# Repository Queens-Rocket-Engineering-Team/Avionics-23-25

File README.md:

# Legacy Repo!!
All QRET avionics hardware and firmware has migrated to:
- https://github.com/Queens-Rocket-Engineering-Team/av-recovery
- https://github.com/Queens-Rocket-Engineering-Team/av-instrumentation
- https://github.com/Queens-Rocket-Engineering-Team/av-telemetry
- http://github.com/Queens-Rocket-Engineering-Team/av-prop
- https://github.com/Queens-Rocket-Engineering-Team/av-power
- https://github.com/Queens-Rocket-Engineering-Team/av-libraries

# QRET Avionics (2023-2026)

This repository is the working space for QRET's 2023-2026 Avionics systems. This includes both hardware design and firmware projects.

If you're contributing, **make sure you're working in a branch other than Main.**

## Branch Naming Conventions
If you create a new branch, make sure its name includes:
- The subject you're working on
- Hardware (HW) or Firmware (FW)

Examples: `Altimeter_HW`, `Sensors_FW`

Currently we're using KiCAD 8.0.6.

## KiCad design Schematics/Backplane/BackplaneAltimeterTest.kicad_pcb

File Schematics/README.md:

# Schematics

This directory contains all schematics involved in this iteration of the Avionics system.

Schematics are made using KiCAD 7.

The `Templates` directory contains a KiCAD project with miscellaneous templates, such as the stack edge connector and template module PCB layout.

## Backplane
- Single large PCB
- Connects all stack "modules" (PCBs)
- Allows communication between modules (CANBUS)
- Cleaner routing for power

## GPS Module
- Acquires GPS signal
- Logs GPS data locally
- Has a daughter-board for the GPS receiver

## Communications Module
- Tracks data from other modules using CANBUS
- Remotely transmits data to ground station

## Altimter Module
- Tracks altitude using pressure and acceleration
- Deploys parachute charges
- Runs on secondary power supply rail
- Logs altitude, pressure, events, etc. locally

## Sensors Module
- Has various on-board and external sensors
- Logs data from above sensors locally

## Power Module
- Provides power to all other modules
	- Primary and Secondary 3.3V rails
	- Primary 5.0V rail
- Facilitates connections between backplane and external devices
	- Batteries
	- Screw switches

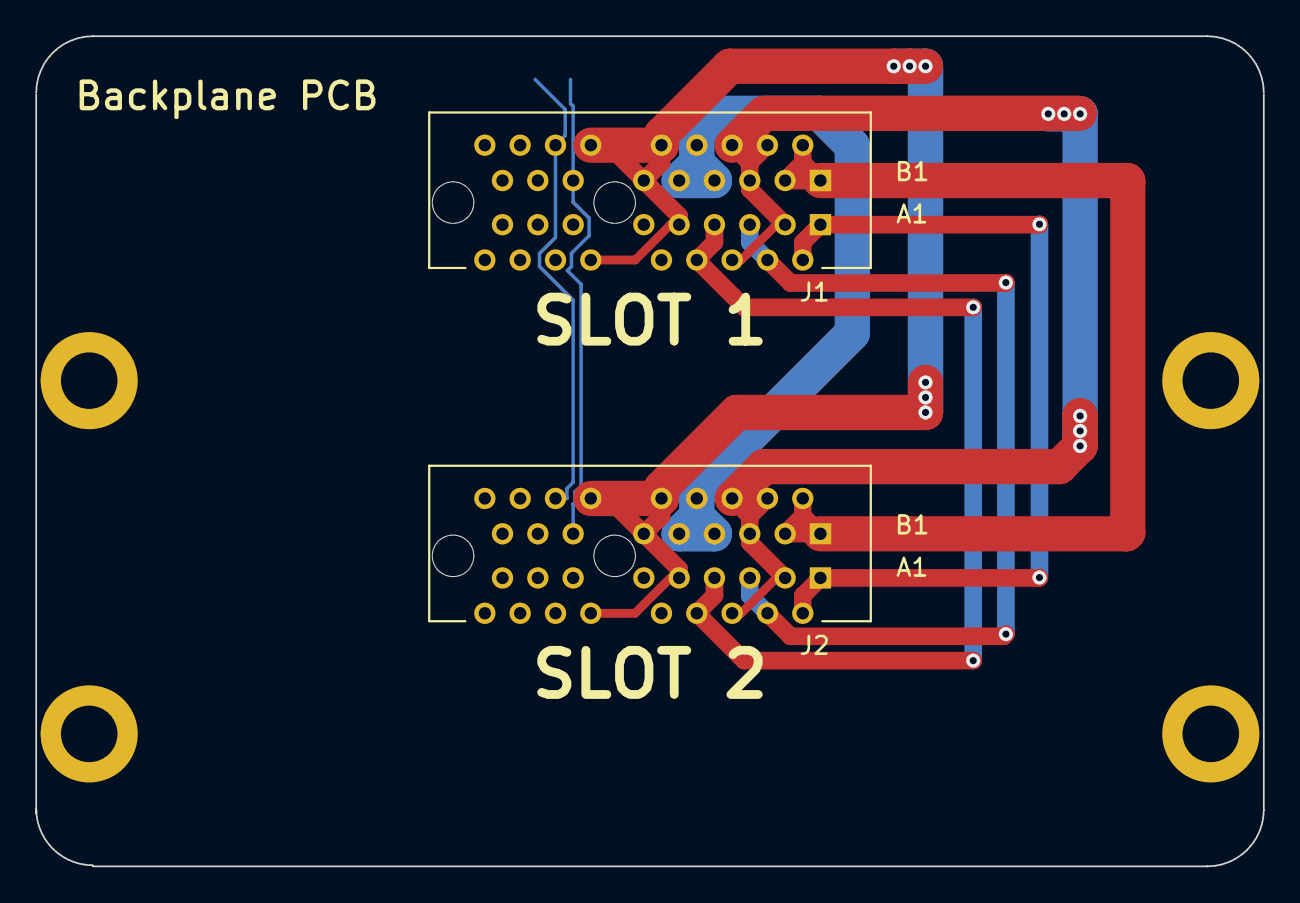
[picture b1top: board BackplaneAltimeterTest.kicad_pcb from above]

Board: 2 copper layers, 69.5 x 47.0 mm, 7 parts (1 on the bottom side), 9 nets.

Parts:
H1, H2, H5, H6: MountingHole; MountingHole_3.2mm_M3_ISO14580_Pad
J1: Edge Connector (SLOT 1); AMPHENOL_10018784-10210TLF
J2: Edge Connector (SLOT 2); AMPHENOL_10018784-10210TLF
R1: 120R; R_0805_2012Metric_Pad1.20x1.40mm_HandSolder

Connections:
3.3V_A: J1.A1 (3.3V_A), J1.A2 (3.3V_A), J2.A1 (3.3V_A), J2.A2 (3.3V_A)
3.3V_B: J1.A7 (3.3V_B), J1.A8 (3.3V_B), J2.A7 (3.3V_B), J2.A8 (3.3V_B)
5.0V_A: J1.A4 (5.0V_A), J1.A5 (5.0V_A), J2.A4 (5.0V_A), J2.A5 (5.0V_A)
BATT_A: J1.B1 (BATT_A), J1.B2 (BATT_A), J1.B3 (BATT_A), J2.B1 (BATT_A), J2.B2 (BATT_A), J2.B3 (BATT_A)
BATT_B: J1.B7 (BATT_B), J1.B8 (BATT_B), J1.B9 (BATT_B), J2.B7 (BATT_B), J2.B8 (BATT_B), J2.B9 (BATT_B)
CAN_H: J1.B14 (CAN_H), J2.B14 (CAN_H), R1.1
CAN_L: J1.B13 (CAN_L), J2.B13 (CAN_L), R1.2
GND1: J1.A3 (GND_A), J1.A6 (GND_A), J1.B4 (GND_A), J1.B5 (GND_A), J1.B6 (GND_A), J2.A3 (GND_A), J2.A6 (GND_A), J2.B4 (GND_A), J2.B5 (GND_A), J2.B6 (GND_A)
GND2: J1.A9 (GND_B), J1.A12 (GND_B), J1.B10 (GND_B), J1.B11 (GND_B), J1.B12 (GND_B), J2.A9 (GND_B), J2.A12 (GND_B), J2.B10 (GND_B), J2.B11 (GND_B), J2.B12 (GND_B)

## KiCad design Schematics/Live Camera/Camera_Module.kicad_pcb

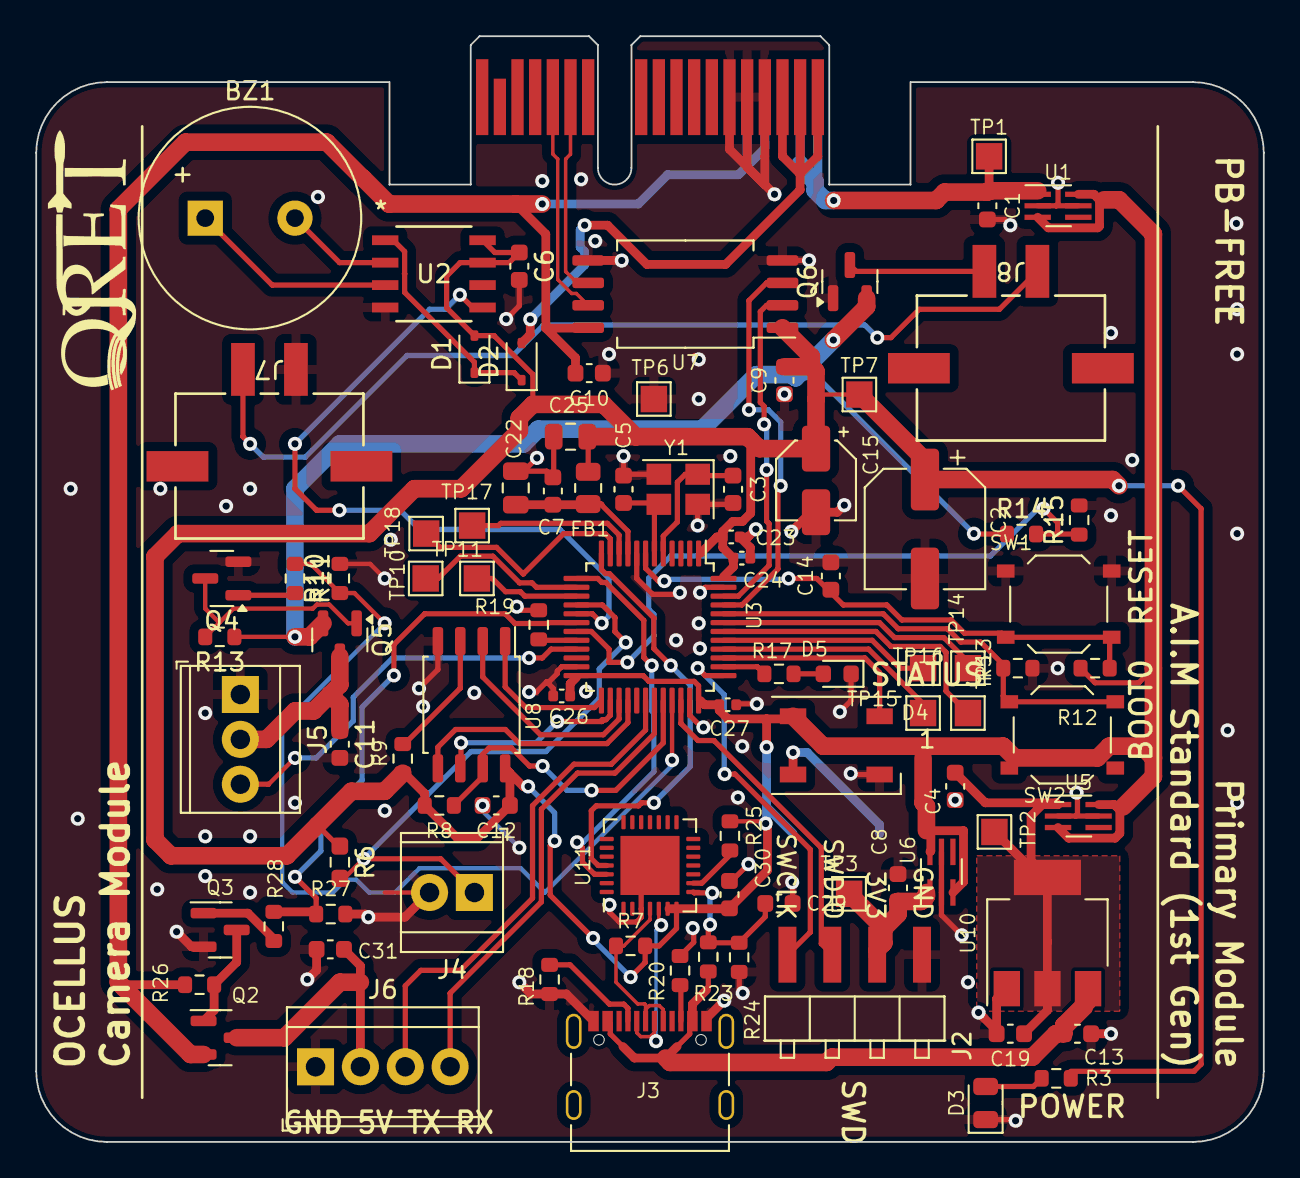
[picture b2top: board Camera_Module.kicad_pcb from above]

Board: 2 copper layers, 69.5 x 62.6 mm, 93 parts (1 on the bottom side), 68 nets.

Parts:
BZ1: PS1240P02BT; Buzzer_12.6x9.5RM5.0
C1, C4, C8, C29: 1uF; C_0603_1608Metric
C2: 100uF; CP_Elec_6.3x5.9
C3, C5: 10p; C_0603_1608Metric
C6, C12, C14: 100nF; C_0603_1608Metric
C7: 10n; C_0603_1608Metric
C9, C10: 0.1u; C_0603_1608Metric
C11, C13, C19, C30, C31: 10uF; C_0603_1608Metric
C15: 10uF; CP_Elec_4x5.4
C22, C25: 1uF; C_0805_2012Metric
C23, C24, C26, C27: 100n; C_0402_1005Metric
D1, D2: 1N5819WS; D_SOD-323
D3: PWR_LED (GRN); LED_0805_2012Metric
D4, D6: WS2812B; LED_WS2812B_PLCC4_5.0x5.0mm_P3.2mm
D5: DB_LED (YLW); LED_0603_1608Metric
FB1: 100R; R_0805_2012Metric
J1: Stack Male Edge Connector; BUS_PCIexpress_x1
J2: SWD_01x04_Pin; SWD_PinHeader_1x04_P2.54mm_Horizontal_SMD
J3: USB_C_Female_USB2_Small; USB_C_DB-108PWB
J4: Therm_In; TerminalBlock_TE_282834-2_1x02_P2.54mm_Horizontal
J5: VTX; TerminalBlock_TE_282834-3_1x03_P2.54mm_Horizontal
J6: RunCam6; TerminalBlock_TE_282834-4_1x04_P2.54mm_Horizontal
J7: VTX_BATT_IN; CONN_2-1445057-2_TYCO
J8: VTX_BATT_SWITCH; CONN_2-1445057-2_TYCO
Q2, Q5, Q6: AO3401A; SOT-23
Q3, Q4: AO3400A; SOT-23
R3: 3.3k; R_0603_1608Metric
R5, R10, R13, R14, R19, R26, R27: 100k; R_0603_1608Metric
R6: 10k; R_0603_1608Metric_Pad0.98x0.95mm_HandSolder
R7: 1.5k; R_0603_1608Metric
R8, R9, R12: 10k; R_0603_1608Metric
R11, R28: 510; R_0603_1608Metric
R15: 20k; R_0603_1608Metric
R17: 680R; R_0603_1608Metric
R18, R20: 5.1k; R_0603_1608Metric
R23: 22k; R_0603_1608Metric
R24: 47k; R_0603_1608Metric
R25: 1k; R_0603_1608Metric
SW1: SW_STM_RESET; SW_Push_1P1T_XKB_TS-1187A
SW2: SW_STM_BOOT_MODE; SW_Push_1P1T_XKB_TS-1187A
TP1: TP_VSTACK; TestPoint_Pad_1.5x1.5mm
TP2: TP_VUSB; TestPoint_Pad_1.5x1.5mm
TP3: TP_VSWD; TestPoint_Pad_1.5x1.5mm
TP6: TP_GND; TestPoint_Pad_1.5x1.5mm
TP7: TP_3V3; TestPoint_Pad_1.5x1.5mm
TP10: PA4; TestPoint_Pad_1.5x1.5mm
TP11: PA5; TestPoint_Pad_1.5x1.5mm
TP13: PB6; TestPoint_Pad_1.5x1.5mm
TP14: PB5; TestPoint_Pad_1.5x1.5mm
TP15: PB4; TestPoint_Pad_1.5x1.5mm
TP16: PB7; TestPoint_Pad_1.5x1.5mm
TP17: PA0; TestPoint_Pad_1.5x1.5mm
TP18: PA1; TestPoint_Pad_1.5x1.5mm
U1, U5, U6: LM66100DCKR; SC-70-6_Handsoldering
U2: TPM8837C-SO1R; SOP-8_TPK
U3: STM32F103CBT6; LQFP-48_7x7mm_P0.5mm
U7: ISO1042BDWVR; SOIC-8 ISO1042BDWV
U8: W25Q128JVS; SOIC-8_5.23x5.23mm_P1.27mm
U10: AMS1117-3.3; SOT-223-3_TabPin2
U11: CP2102N-Axx-xQFN28; QFN-28-1EP_5x5mm_P0.5mm_EP3.35x3.35mm
Y1: X322516MMB4SI; Crystal_SMD_3225-4Pin_3.2x2.5mm

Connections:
5V_USB: C13.1, J3.A4 (VBUS), J3.A9 (VBUS), J3.B4 (VBUS), J3.B9 (VBUS), R23.2, U10.3 (VI)
+3.3V: C2.1, C6.1, C9.2, C12.1, C15.1, C23.1, C24.1, C25.1, C26.1, C27.1, C30.2, D1.2 (A), D4.1 (VDD), D6.1 (VDD), FB1.2, R3.2, R6.1, R7.1, R8.2, R9.2, R12.2, R25.2, SW2.2, TP7.1, U1.3 (*CE), U1.6 (VOUT), U2.7 (NSLEEP), U2.8 (VCC), U3.1 (VBAT), U3.24 (VDD), U3.36 (VDD), U3.48 (VDD), U5.3 (*CE), U5.6 (VOUT), U6.3 (*CE), U6.6 (VOUT), U7.1 (VCC1), U8.8 (VCC), U11.6 (VDD), U11.7 (VREGIN)
+3.3VA: C7.1, C22.1, FB1.1, U3.9 (VDDA)
+5V: C10.2, J1.A4 (5.0V_A), J1.A5 (5.0V_A), Q2.2 (S), R26.1, U7.8 (VCC2)
+BATT: D2.2 (A), J1.B1 (BATT_A), J1.B2 (BATT_A), J1.B3 (BATT_A)
BOOT0: R5.2, SW2.1, U3.44 (BOOT0)
BOOT1: R19.2, U3.20 (PB2)
BUZZER_A: U2.6 (IN1), U3.29 (PA8)
BUZZER_B: U2.5 (IN2), U3.17 (PA7)
CAM_5V: C31.1, J6.2, Q2.3 (D)
CAM_PWR: R27.1, R28.1, U3.18 (PB0)
CAM_RX: J6.4, U3.31 (PA10)
CAM_TX: J6.3, U3.30 (PA9)
CAN_H: J1.B14 (CAN_H), U7.7 (CANH)
CAN_L: J1.B13 (CAN_L), U7.6 (CANL)
CAN_RX: U3.45 (PB8), U7.3 (RXD)
CAN_TX: U3.46 (PB9), U7.2 (TXD)
CS_FL: U3.25 (PB12), U8.1 (~CS)
DB_LED: R17.2, U3.38 (PA15)
GND: C1.2, C2.2, C3.2, C4.2, C5.2, C6.2, C7.2, C8.2, C9.1, C10.1, C11.2, C12.2, C13.2, C14.2, C15.2, C19.2, C22.2, C23.2, C24.2, C25.2, C26.2, C27.2, C29.1, C30.1, C31.2, D3.1 (K), D4.3 (VSS), D5.1 (K), D6.3 (VSS), J1.A3 (GND_A), J1.A6 (GND_A), J1.B4 (GND_A), J1.B5 (GND_A), J1.B6 (GND_A), J2.1 (GND), J3.A1 (GND), J3.A12 (GND), J3.B1 (GND), J3.B12 (GND), J4.2, J5.1, J6.1, J7.1, Q3.2 (S), Q4.2 (S), Q6.1 (G), R5.1, R10.2, R15.2, R18.2, R19.1, R20.2, R24.1, R27.2, SW1.1, TP6.1, U1.2 (GND), U1.5 (ST), U2.4 (GND), U3.8 (VSSA), U3.23 (VSS), U3.35 (VSS), U3.47 (VSS), U5.2 (GND), U5.5 (ST), U6.2 (GND), U6.5 (ST), U7.4 (GND1), U7.5 (GND2), U8.4 (GND), U10.1 (GND), U11.3 (GND), U11.29 (GND), Y1.2, Y1.4
MISO_FL: U3.27 (PB14), U8.2 (DO(IO1))
MOSI_FL: U3.28 (PB15), U8.5 (DI(IO0))
unnamed: BZ1.2 (+), U2.2 (OUT1)
unnamed: BZ1.1 (-), U2.3 (OUT2)
unnamed: D1.1 (K), D2.1 (K), U2.1 (VM)
unnamed: D3.2 (A), R3.1
unnamed: D4.2 (DOUT), D6.4 (DIN)
unnamed: D5.2 (A), R17.1
unnamed: J3.A5 (CC1), R18.1
unnamed: J3.B5 (CC2), R20.1
unnamed: J7.2, J8.1
unnamed: Q2.1 (G), Q3.3 (D), R26.2
unnamed: Q3.1 (G), R28.2
unnamed: Q4.3 (D), Q5.1 (G), R13.2
unnamed: Q4.1 (G), R11.2
unnamed: J8.2, Q6.3 (D)
unnamed: TP17.1, U3.10 (PA0)
unnamed: TP18.1, U3.11 (PA1)
unnamed: TP10.1, U3.14 (PA4)
unnamed: TP11.1, U3.15 (PA5)
unnamed: TP15.1, U3.40 (PB4)
unnamed: TP14.1, U3.41 (PB5)
unnamed: TP13.1, U3.42 (PB6)
unnamed: TP16.1, U3.43 (PB7)
unnamed: R9.1, U8.3 (IO2)
unnamed: C29.2, R23.1, R24.2, U11.8 (VBUS)
unnamed: R25.1, U11.9 (~RST)
OSC_IN: C3.1, U3.5 (PD0), Y1.1
OSC_OUT: C5.1, U3.6 (PD1), Y1.3
RESET_FL: R8.1, U3.32 (PA11), U8.7 (IO3)
RGB_DATA: D4.4 (DIN), U3.39 (PB3)
SCK_FL: U3.26 (PB13), U8.6 (CLK)
STM_RESET: C14.1, R12.1, SW1.2, U3.7 (NRST)
SWCLK: J2.4 (SWCLK), U3.37 (PA14)
SWDIO: J2.3 (SWDIO), U3.34 (PA13)
USB_D+: J3.A6 (D+), J3.B6 (D+), R7.2, U11.4 (D+)
USB_D-: J3.A7 (D-), J3.B7 (D-), U11.5 (D-)
USB_RX: U3.13 (PA3), U11.26 (TXD)
USB_TX: U3.12 (PA2), U11.25 (RXD)
VTX_BATT: Q5.2 (S), Q6.2 (S), R13.1, R14.1
VTX_BATT_SENSE: R14.2, R15.1, U3.19 (PB1)
VTX_DATA: J5.3, U3.21 (PB10)
VTX_PWR: R10.1, R11.1, U3.33 (PA12)
VTX_V+: C11.1, J5.2, Q5.3 (D)
V_PSU: C1.1, J1.A1 (3.3V_A), J1.A2 (3.3V_A), TP1.1, U1.1 (VIN)
V_REGUSB: C4.1, C19.1, TP2.1, U5.1 (VIN), U10.2 (VO)
V_SWD: C8.1, J2.2 (3V3), TP3.1, U6.1 (VIN)
V_THERM: J4.1, R6.2, U3.16 (PA6)

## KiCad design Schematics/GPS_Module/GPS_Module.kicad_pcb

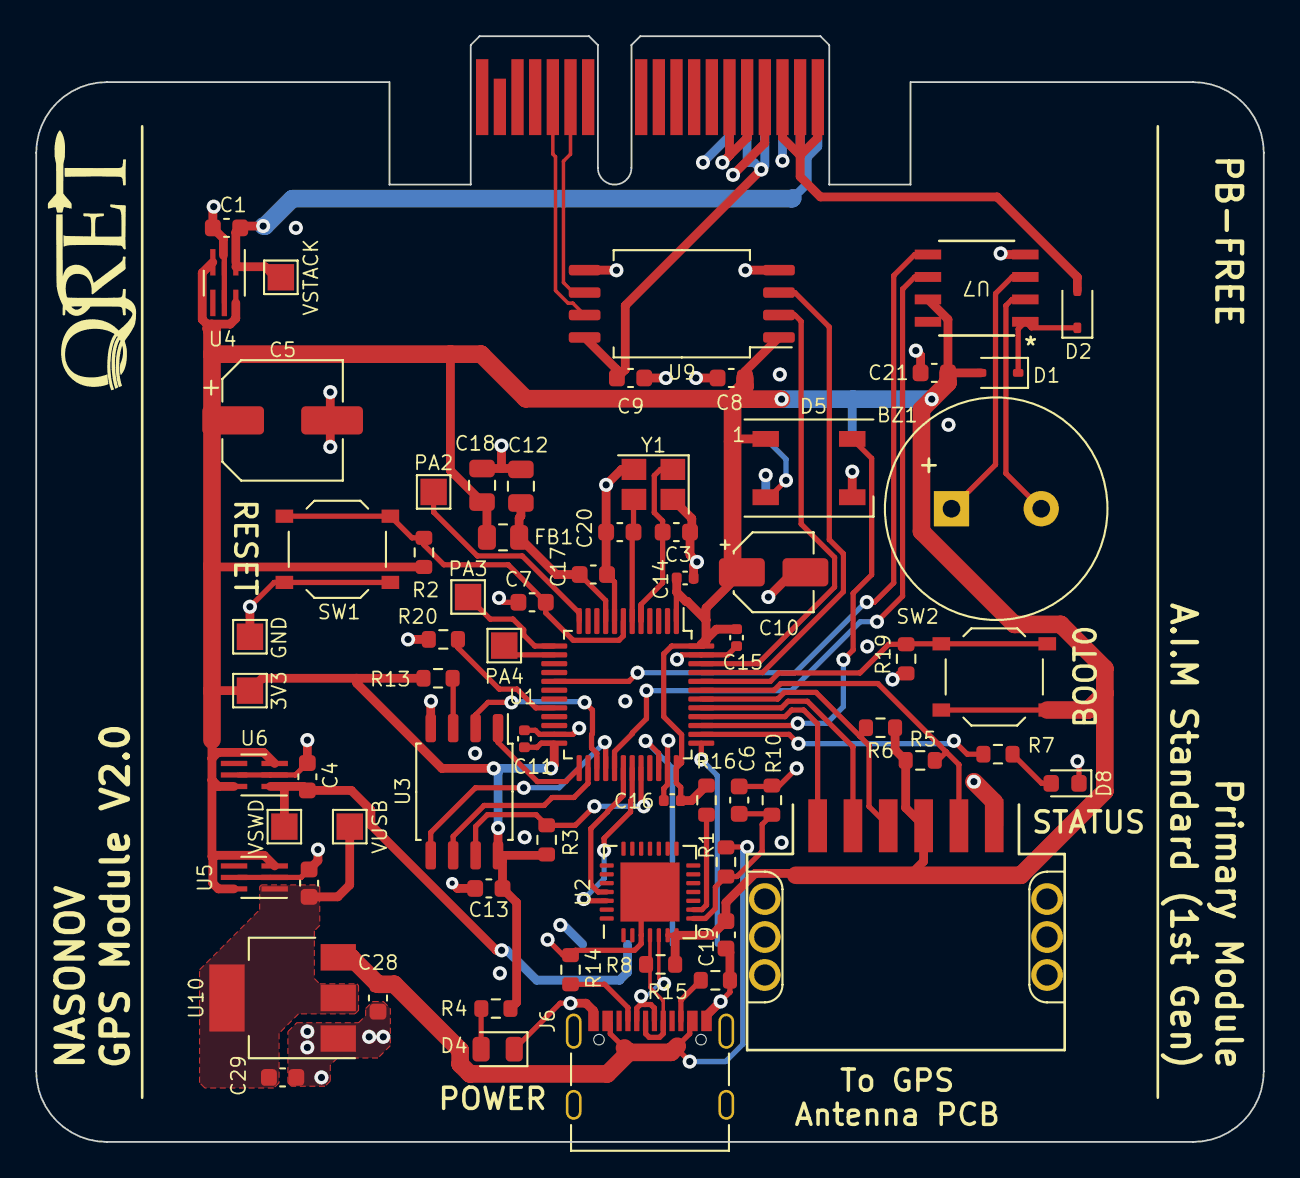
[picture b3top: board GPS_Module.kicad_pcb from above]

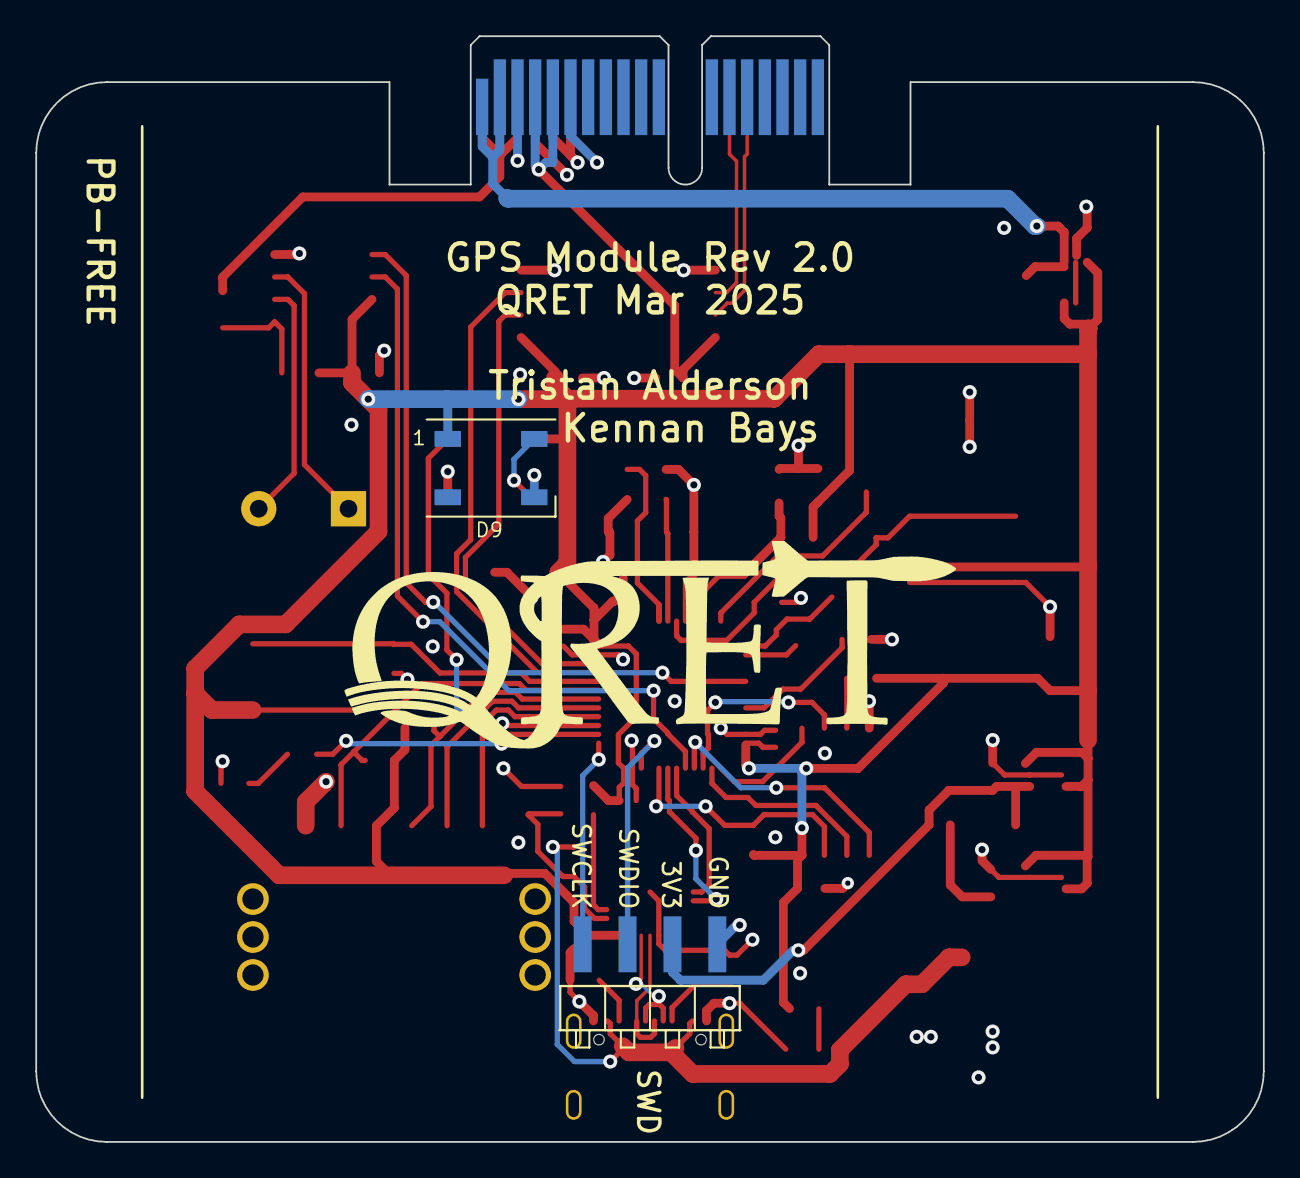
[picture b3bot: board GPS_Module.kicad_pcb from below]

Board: 4 copper layers, 69.5 x 62.6 mm, 70 parts (2 on the bottom side), 51 nets.

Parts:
BZ1: PS1240P02BT; Buzzer_12.6x9.5RM5.0
C1, C2, C4, C6: 1uF; C_0603_1608Metric
C3, C20: 10p; C_0603_1608Metric
C5: 100uF; CP_Elec_6.3x5.9
C7, C13, C21: 100nF; C_0603_1608Metric
C8, C9: 0.1u; C_0603_1608Metric
C10: 10uF; CP_Elec_4x5.4
C11, C14, C15, C16: 100n; C_0402_1005Metric
C12, C18: 1uF; C_0805_2012Metric
C17: 10n; C_0603_1608Metric
C19, C28, C29: 10uF; C_0603_1608Metric
D1, D2: 1N5819WS; D_SOD-323
D4: PWR_LED (GRN); LED_0805_2012Metric
D5, D9: WS2812B; LED_WS2812B_PLCC4_5.0x5.0mm_P3.2mm
D8: DB_LED (YLW); LED_0603_1608Metric
FB1: 100R; R_0805_2012Metric
J1: GT8E-6P-2H(55); CONN_GT8E-6P-2H(55)
J2: SWD_01x04_Pin; SWD_PinHeader_1x04_P2.54mm_Horizontal_SMD
J4: Stack Male Edge Connector; BUS_PCIexpress_x1
J6: USB_C_Female_USB2_Small; USB_C_DB-108PWB
R1: 22k; R_0603_1608Metric
R2, R3, R13: 10k; R_0603_1608Metric
R4: 3.3k; R_0603_1608Metric
R5, R6: 2.2k; R_0603_1608Metric
R7: 680R; R_0603_1608Metric
R8: 1.5k; R_0603_1608Metric
R10: 47k; R_0603_1608Metric
R14, R15: 5.1k; R_0603_1608Metric
R16: 1k; R_0603_1608Metric
R19, R20: 100k; R_0603_1608Metric
SW1: SW_STM_RESET; SW_Push_1P1T_XKB_TS-1187A
SW2: SW_STM_BOOT_MODE; SW_Push_1P1T_XKB_TS-1187A
TP1: VSTACK; TestPoint_Pad_1.5x1.5mm
TP2: VUSB; TestPoint_Pad_1.5x1.5mm
TP3: VSWD; TestPoint_Pad_1.5x1.5mm
TP4: PA4; TestPoint_Pad_1.5x1.5mm
TP6: GND; TestPoint_Pad_1.5x1.5mm
TP7: 3V3; TestPoint_Pad_1.5x1.5mm
TP10: PA2; TestPoint_Pad_1.5x1.5mm
TP11: PA3; TestPoint_Pad_1.5x1.5mm
U1: STM32F103CBT6; LQFP-48_7x7mm_P0.5mm
U2: CP2102N-Axx-xQFN28; QFN-28-1EP_5x5mm_P0.5mm_EP3.35x3.35mm
U3: W25Q128JVS; SOIC-8_5.23x5.23mm_P1.27mm
U4, U5, U6: LM66100DCKR; SC-70-6_Handsoldering
U7: TPM8837C-SO1R; SOP-8_TPK
U9: ISO1042BQDWVR; SOIC-8 ISO1042BDWV
U10: AMS1117-3.3; SOT-223-3_TabPin2
Y1: X322516MMB4SI; Crystal_SMD_3225-4Pin_3.2x2.5mm

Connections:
5V_RAW: C28.1, J6.A4 (VBUS), J6.A9 (VBUS), J6.B4 (VBUS), J6.B9 (VBUS), R1.2, U10.3 (VI)
+3.3V: C5.1, C8.2, C10.1, C11.1, C13.1, C14.1, C15.1, C16.1, C18.1, C19.2, C21.1, D1.2 (A), D5.1 (VDD), D9.1 (VDD), FB1.2, J1.3, R2.2, R3.2, R4.2, R5.2, R6.1, R8.1, R13.2, R16.2, SW2.2, TP7.1, U1.1 (VBAT), U1.24 (VDD), U1.36 (VDD), U1.48 (VDD), U2.6 (VDD), U2.7 (VREGIN), U3.8 (VCC), U4.3 (*CE), U4.6 (VOUT), U5.3 (*CE), U5.6 (VOUT), U6.3 (*CE), U6.6 (VOUT), U7.7 (NSLEEP), U7.8 (VCC), U9.1 (VCC1)
+3.3VA: C12.1, C17.1, FB1.1, U1.9 (VDDA)
+5V: C9.2, J4.A4 (5.0V_A), J4.A5 (5.0V_A), U9.8 (VCC2)
+BATT: D2.2 (A), J4.B1 (BATT_A), J4.B2 (BATT_A), J4.B3 (BATT_A)
BOOT0: R19.2, SW2.1, U1.44 (BOOT0)
BOOT1: R20.2, U1.20 (PB2)
BUZZER_A: U1.29 (PA8), U7.6 (IN1)
BUZZER_B: U1.17 (PA7), U7.5 (IN2)
CAN_H: J4.B14 (CAN_H), U9.7 (CANH)
CAN_L: J4.B13 (CAN_L), U9.6 (CANL)
CAN_RX: U1.45 (PB8), U9.3 (RXD)
CAN_TX: U1.46 (PB9), U9.2 (TXD)
CS_FL: U1.25 (PB12), U3.1 (~CS)
DB_LED: R7.2, U1.38 (PA15)
EXTINT_GPS: J1.5, U1.41 (PB5)
GND: C1.2, C2.2, C3.2, C4.2, C5.2, C6.1, C7.2, C8.1, C9.1, C10.2, C11.2, C12.2, C13.2, C14.2, C15.2, C16.2, C17.2, C18.2, C19.1, C20.2, C21.2, C28.2, C29.2, D4.1 (K), D5.3 (VSS), D8.1 (K), D9.3 (VSS), J1.1, J2.1 (GND), J4.A3 (GND_A), J4.A6 (GND_A), J4.B4 (GND_A), J4.B5 (GND_A), J4.B6 (GND_A), J6.A1 (GND), J6.A12 (GND), J6.B1 (GND), J6.B12 (GND), R10.1, R14.2, R15.2, R19.1, R20.1, SW1.1, TP6.1, U1.8 (VSSA), U1.23 (VSS), U1.35 (VSS), U1.47 (VSS), U2.3 (GND), U2.29 (GND), U3.4 (GND), U4.2 (GND), U4.5 (ST), U5.2 (GND), U5.5 (ST), U6.2 (GND), U6.5 (ST), U7.4 (GND), U9.4 (GND1), U9.5 (GND2), U10.1 (GND), Y1.2, Y1.4
MISO_FL: U1.27 (PB14), U3.2 (DO(IO1))
MOSI_FL: U1.28 (PB15), U3.5 (DI(IO0))
unnamed: BZ1.2 (+), U7.2 (OUT1)
unnamed: BZ1.1 (-), U7.3 (OUT2)
unnamed: D1.1 (K), D2.1 (K), U7.1 (VM)
unnamed: D4.2 (A), R4.1
unnamed: D5.2 (DOUT), D9.4 (DIN)
unnamed: D8.2 (A), R7.1
unnamed: J6.A5 (CC1), R14.1
unnamed: J6.B5 (CC2), R15.1
unnamed: TP10.1, U1.12 (PA2)
unnamed: TP11.1, U1.13 (PA3)
unnamed: TP4.1, U1.14 (PA4)
unnamed: C6.2, R1.1, R10.2, U2.8 (VBUS)
unnamed: R16.1, U2.9 (~RST)
unnamed: R13.1, U3.3 (IO2)
OSC_IN: C3.1, U1.5 (PD0), Y1.1
OSC_OUT: C20.1, U1.6 (PD1), Y1.3
RESET_FL: R3.1, U1.32 (PA11), U3.7 (IO3)
RGB_DATA: D5.4 (DIN), U1.39 (PB3)
RST_GPS: J1.6, U1.40 (PB4)
SCK_FL: U1.26 (PB13), U3.6 (CLK)
SCL_GPS: J1.4, R6.2, U1.42 (PB6)
SDA_GPS: J1.2, R5.1, U1.43 (PB7)
STM_RESET: C7.1, R2.1, SW1.2, U1.7 (NRST)
SWCLK: J2.4 (SWCLK), U1.37 (PA14)
SWDIO: J2.3 (SWDIO), U1.34 (PA13)
USB_D+: J6.A6 (D+), J6.B6 (D+), R8.2, U2.4 (D+)
USB_D-: J6.A7 (D-), J6.B7 (D-), U2.5 (D-)
USB_RX: U1.31 (PA10), U2.26 (TXD)
USB_TX: U1.30 (PA9), U2.25 (RXD)
V_PSU: C1.1, J4.A1 (3.3V_A), J4.A2 (3.3V_A), TP1.1, U4.1 (VIN)
V_REGUSB: C2.1, C29.1, TP2.1, U5.1 (VIN), U10.2 (VO)
V_SWD: C4.1, J2.2 (3V3), TP3.1, U6.1 (VIN)

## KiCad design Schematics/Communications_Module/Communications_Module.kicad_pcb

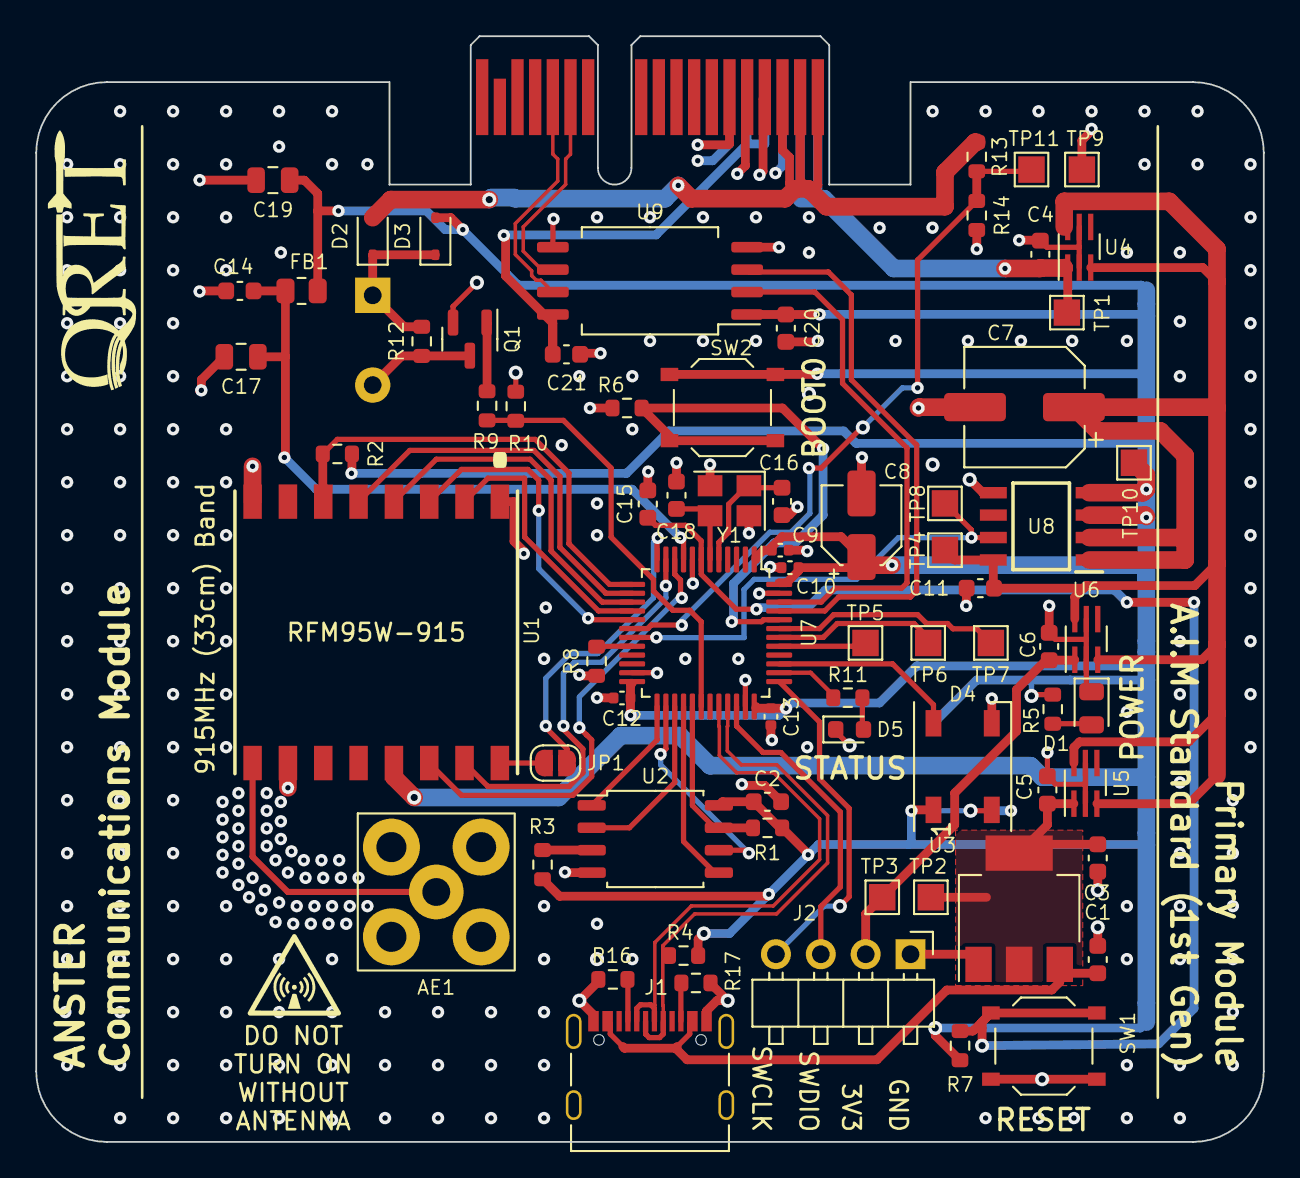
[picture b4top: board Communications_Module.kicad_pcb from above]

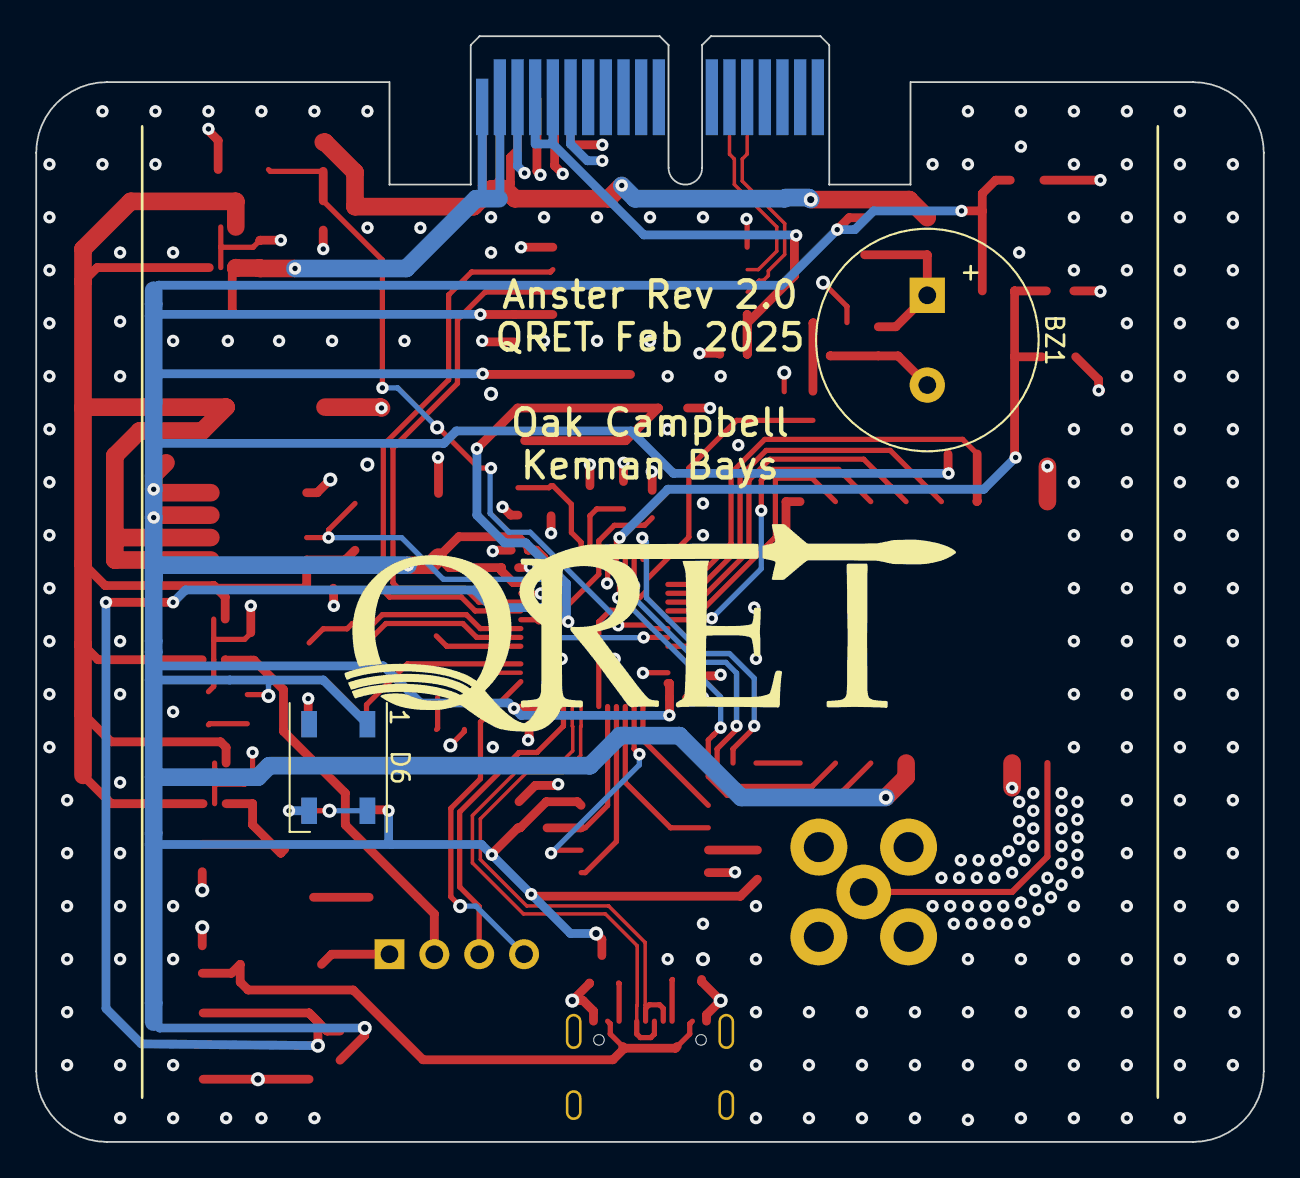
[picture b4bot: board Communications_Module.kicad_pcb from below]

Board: 4 copper layers, 69.5 x 62.6 mm, 74 parts (2 on the bottom side), 55 nets.

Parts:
AE1: Antenna; KH-SMA-K513-G
BZ1: PKM13EPYH4000; Buzzer_12.6x9.5RM5.0
C1, C3: 10uF; C_0603_1608Metric
C2, C15: 100nF; C_0603_1608Metric
C4, C5, C6: 1uF; C_0603_1608Metric
C7: 100uF; CP_Elec_6.3x5.9
C8: 10uF; CP_Elec_4x5.4
C9, C10, C12, C13: 100n; C_0402_1005Metric
C11: 0.1uF; C_0603_1608Metric
C14: 10n; C_0603_1608Metric
C16, C18: 10p; C_0603_1608Metric
C17, C19: 1uF; C_0805_2012Metric
C20, C21: 0.1u; C_0603_1608Metric
D1: PWR_LED (GRN); LED_0805_2012Metric
D2, D3: 1N5819WS; D_SOD-323
D4, D6: WS2812B; LED_WS2812B_PLCC4_5.0x5.0mm_P3.2mm
D5: DB_LED (YLW); LED_0603_1608Metric
FB1: 100R; R_0805_2012Metric
J1: USB_C_Female_USB2_Small; USB_C_DB-108PWB
J2: SWD_01x04_Pin; SWD_PinHeader_1x04_P2.54mm_Horizontal
J3: Stack Male Edge Connector; BUS_PCIexpress_x1
JP1: DIO5_EN; SolderJumper-2_P1.3mm_Open_RoundedPad1.0x1.5mm
Q1: AO3400A; SOT-23
R1, R2, R3, R7, R10, R14: 10k; R_0603_1608Metric
R4: 1.5k; R_0603_1608Metric
R5: 1.2k; R_0603_1608Metric
R6, R8: 100k; R_0603_1608Metric
R9: 510R; R_0603_1608Metric
R11: 680R; R_0603_1608Metric
R12: 1k; R_0603_1608Metric
R13: 30k; R_0603_1608Metric
R16, R17: 5.1k; R_0603_1608Metric
SW1: SW_STM_RESET; SW_Push_1P1T_XKB_TS-1187A
SW2: SW_STM_BOOT_MODE; SW_Push_1P1T_XKB_TS-1187A
TP1: TP_VSTACK; TestPoint_Pad_1.5x1.5mm
TP2: TP_VUSB; TestPoint_Pad_1.5x1.5mm
TP3: TP_VSWD; TestPoint_Pad_1.5x1.5mm
TP4: TP_MUX; TestPoint_Pad_1.5x1.5mm
TP5: TP_PB5; TestPoint_Pad_1.5x1.5mm
TP6: TP_PB6; TestPoint_Pad_1.5x1.5mm
TP7: TP_PB7; TestPoint_Pad_1.5x1.5mm
TP8: TP_ISENSE; TestPoint_Pad_1.5x1.5mm
TP9: TP_GND; TestPoint_Pad_1.5x1.5mm
TP10: TP_3V3; TestPoint_Pad_1.5x1.5mm
TP11: TP_BSENSE; TestPoint_Pad_1.5x1.5mm
U1: RFM95W-915; RFM95W
U2: W25Q128JVS; SOIC-8_5.23x5.23mm_P1.27mm
U3: AMS1117-3.3; SOT-223-3_TabPin2
U4, U5, U6: LM66100DCKR; SC-70-6_Handsoldering
U7: STM32F103CBT6; LQFP-48_7x7mm_P0.5mm
U8: ACS70331EOLC; SOIC127P600X175-8N
U9: ISO1042BDWVR; SOIC-8 ISO1042BDWV
Y1: X322516MMB4SI; Crystal_SMD_3225-4Pin_3.2x2.5mm

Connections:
+3.3V: C2.1, C8.1, C9.1, C10.1, C12.1, C13.1, C19.1, C20.2, D3.2 (A), D4.1 (VDD), D6.1 (VDD), FB1.2, R1.2, R2.2, R3.2, R4.2, R5.2, R7.2, SW2.2, TP10.1, U1.13 (3.3V), U2.8 (VCC), U7.1 (VBAT), U7.24 (VDD), U7.36 (VDD), U7.48 (VDD), U8.3 (IP-), U8.4 (IP-), U9.1 (VCC1)
+3.3VA: C14.1, C17.1, FB1.1, U7.9 (VDDA)
+5V: C21.2, J3.A4 (5.0V_A), J3.A5 (5.0V_A), U9.8 (VCC2)
+BATT: D2.2 (A), J3.B1 (BATT_A), J3.B2 (BATT_A), J3.B3 (BATT_A), R13.1
/USB_5V: C1.1, J1.A4 (VBUS), J1.A9 (VBUS), J1.B4 (VBUS), J1.B9 (VBUS), U3.3 (VI)
BATT_SENSE: R13.2, R14.1, TP11.1, U7.18 (PB0)
BOOT0: R6.2, SW2.1, U7.44 (BOOT0)
BOOT1: R8.2, U7.20 (PB2)
BUZZER: R9.2, R10.2, U7.30 (PA9)
CAN_H: J3.B14 (CAN_H), U9.7 (CANH)
CAN_L: J3.B13 (CAN_L), U9.6 (CANL)
CAN_RX: U7.45 (PB8), U9.3 (RXD)
CAN_TX: U7.46 (PB9), U9.2 (TXD)
CS_FL: U2.1 (~CS), U7.25 (PB12)
CS_RF: U1.5 (NSS), U7.14 (PA4)
CURR_SENSE: TP8.1, U7.19 (PB1), U8.7 (VOUT)
DB_LED: R11.2, U7.38 (PA15)
DIO0_RF: U1.14 (DIO0), U7.10 (PA0)
DIO1_RF: U1.15 (DIO1), U7.11 (PA1)
DIO2_RF: JP1.2 (B), U7.12 (PA2)
GND: AE1.2 (Shield), C1.2, C2.2, C3.2, C4.2, C5.2, C6.2, C7.2, C8.2, C9.2, C10.2, C11.2, C12.2, C13.2, C14.2, C15.2, C16.2, C17.2, C18.2, C19.2, C20.1, C21.1, D1.1 (K), D4.3 (VSS), D5.1 (K), D6.3 (VSS), J1.A1 (GND), J1.A12 (GND), J1.B1 (GND), J1.B12 (GND), J2.1 (GND), J3.A3 (GND_A), J3.A6 (GND_A), J3.B4 (GND_A), J3.B5 (GND_A), J3.B6 (GND_A), Q1.2 (S), R6.1, R8.1, R10.1, R14.2, R16.2, R17.2, SW1.1, TP9.1, U1.1 (GND), U1.8 (GND), U1.10 (GND), U2.4 (GND), U3.1 (GND), U4.2 (GND), U4.5 (ST), U5.2 (GND), U5.5 (ST), U6.2 (GND), U6.5 (ST), U7.8 (VSSA), U7.23 (VSS), U7.35 (VSS), U7.47 (VSS), U8.5 (GND), U9.4 (GND1), U9.5 (GND2), Y1.2, Y1.4
MISO_FL: U2.2 (DO(IO1)), U7.27 (PB14)
MISO_RF: U1.2 (MISO), U7.16 (PA6)
MOSI_FL: U2.5 (DI(IO0)), U7.28 (PB15)
MOSI_RF: U1.3 (MOSI), U7.17 (PA7)
unnamed: AE1.1 (A), U1.9 (ANT)
unnamed: BZ1.2 (+), Q1.3 (D), R12.1
unnamed: BZ1.1 (-), D2.1 (K), D3.1 (K), R12.2
unnamed: D1.2 (A), R5.1
unnamed: D4.2 (DOUT), D6.4 (DIN)
unnamed: D5.2 (A), R11.1
unnamed: J1.A5 (CC1), R16.1
unnamed: J1.B5 (CC2), R17.1
unnamed: JP1.1 (A), U1.16 (DIO2)
unnamed: Q1.1 (G), R9.1
unnamed: R3.1, U2.3 (IO2)
unnamed: TP5.1, U7.41 (PB5)
unnamed: TP6.1, U7.42 (PB6)
unnamed: TP7.1, U7.43 (PB7)
OSC_IN: C16.1, U7.5 (PD0), Y1.1
OSC_OUT: C18.1, U7.6 (PD1), Y1.3
RESET_FL: R1.1, U2.7 (IO3), U7.29 (PA8)
RESET_RF: R2.1, U1.6 (RESET), U7.13 (PA3)
RGB_DATA: D4.4 (DIN), U7.39 (PB3)
SCK_FL: U2.6 (CLK), U7.26 (PB13)
SCK_RF: U1.4 (SCK), U7.15 (PA5)
STM_RESET: C15.1, R7.1, SW1.2, U7.7 (NRST)
SWCLK: J2.4 (SWCLK), U7.37 (PA14)
SWDIO: J2.3 (SWDIO), U7.34 (PA13)
USB_D+: J1.A6 (D+), J1.B6 (D+), R4.1, U7.33 (PA12)
USB_D-: J1.A7 (D-), J1.B7 (D-), U7.32 (PA11)
V_MUX: C7.1, C11.1, TP4.1, U4.3 (*CE), U4.6 (VOUT), U5.3 (*CE), U5.6 (VOUT), U6.3 (*CE), U6.6 (VOUT), U8.1 (IP+), U8.2 (IP+), U8.8 (VCC)
V_PSU: C4.1, J3.A1 (3.3V_A), J3.A2 (3.3V_A), TP1.1, U4.1 (VIN)
V_REGUSB: C3.1, C5.1, TP2.1, U3.2 (VO), U5.1 (VIN)
V_SWD: C6.1, J2.2 (3V3), TP3.1, U6.1 (VIN)
